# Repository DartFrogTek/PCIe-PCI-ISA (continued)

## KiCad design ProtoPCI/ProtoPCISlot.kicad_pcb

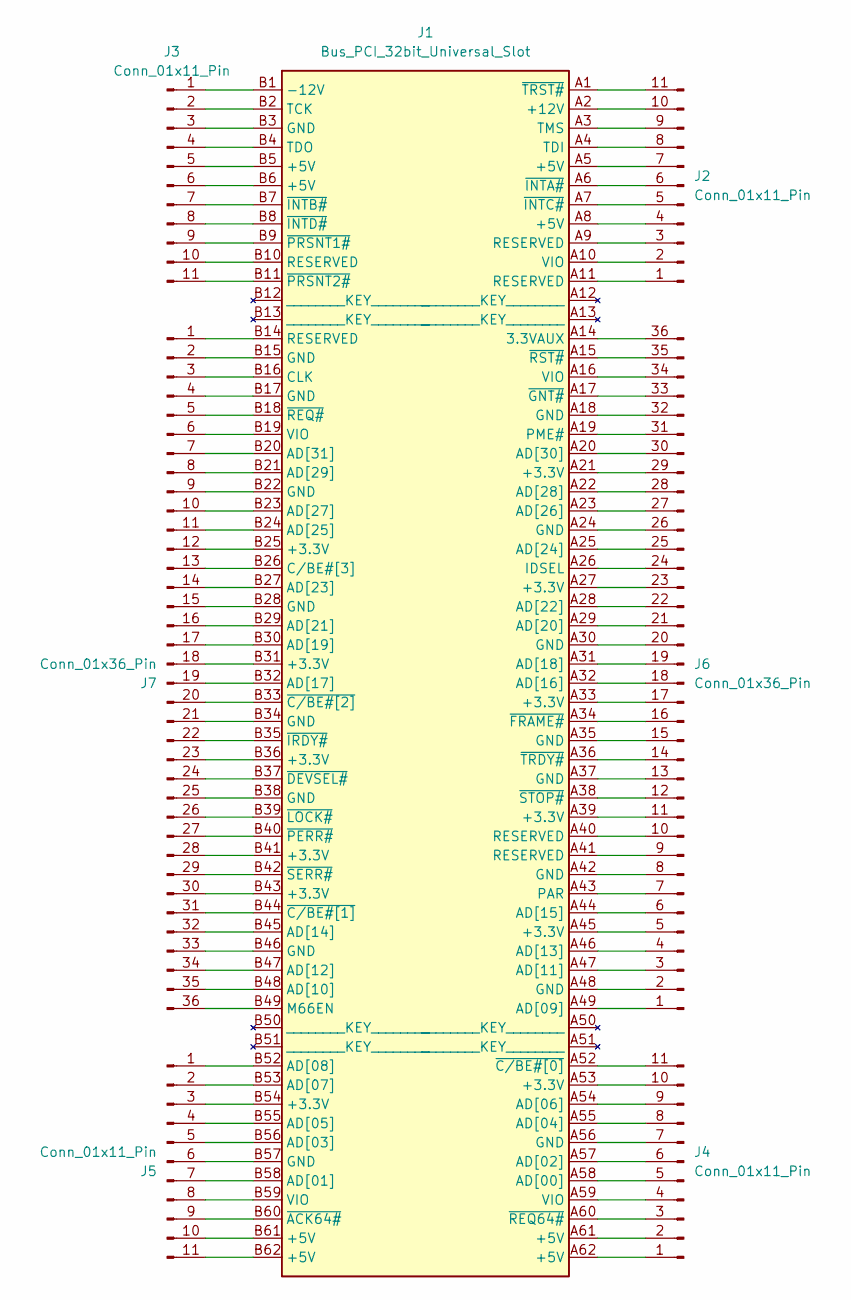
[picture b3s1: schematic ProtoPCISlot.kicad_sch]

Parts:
J1: Bus_PCI_32bit_Universal_Slot; 51451541
J2, J3, J4, J5: Conn_01x11_Pin; PinHeader_1x11_P2.54mm_Vertical
J6, J7: Conn_01x36_Pin; PinHeader_1x36_P2.54mm_Vertical

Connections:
unnamed: J1.A14 (3.3VAUX), J6.36
unnamed: J1.A2 (+12V), J2.10
unnamed: J1.B1 (-12V), J3.1
unnamed: J1.A58 (AD[00]), J4.5
unnamed: J1.B58 (AD[01]), J5.7
unnamed: J1.A57 (AD[02]), J4.6
unnamed: J1.B56 (AD[03]), J5.5
unnamed: J1.A55 (AD[04]), J4.8
unnamed: J1.B55 (AD[05]), J5.4
unnamed: J1.A54 (AD[06]), J4.9
unnamed: J1.B53 (AD[07]), J5.2
unnamed: J1.B52 (AD[08]), J5.1
unnamed: J1.A49 (AD[09]), J6.1
unnamed: J1.B48 (AD[10]), J7.35
unnamed: J1.A47 (AD[11]), J6.3
unnamed: J1.B47 (AD[12]), J7.34
unnamed: J1.A46 (AD[13]), J6.4
unnamed: J1.B45 (AD[14]), J7.32
unnamed: J1.A44 (AD[15]), J6.6
unnamed: J1.A32 (AD[16]), J6.18
unnamed: J1.B32 (AD[17]), J7.19
unnamed: J1.A31 (AD[18]), J6.19
unnamed: J1.B30 (AD[19]), J7.17
unnamed: J1.A29 (AD[20]), J6.21
unnamed: J1.B29 (AD[21]), J7.16
unnamed: J1.A28 (AD[22]), J6.22
unnamed: J1.B27 (AD[23]), J7.14
unnamed: J1.A25 (AD[24]), J6.25
unnamed: J1.B24 (AD[25]), J7.11
unnamed: J1.A23 (AD[26]), J6.27
unnamed: J1.B23 (AD[27]), J7.10
unnamed: J1.A22 (AD[28]), J6.28
unnamed: J1.B21 (AD[29]), J7.8
unnamed: J1.A20 (AD[30]), J6.30
unnamed: J1.B20 (AD[31]), J7.7
unnamed: J1.B16 (CLK), J7.3
unnamed: J1.B26 (C/BE#[3]), J7.13
unnamed: J1.A26 (IDSEL), J6.24
unnamed: J1.B49 (M66EN), J7.36
unnamed: J1.A43 (PAR), J6.7
unnamed: J1.A19 (PME#), J6.31
unnamed: J1.B2 (TCK), J3.2
unnamed: J1.A4 (TDI), J2.8
unnamed: J1.B4 (TDO), J3.4
unnamed: J1.A3 (TMS), J2.9
unnamed: J1.B60 (~ACK64#), J5.9
unnamed: J1.A52 (~C/BE#[0]), J4.11
unnamed: J1.B44 (~C/BE#[1]), J7.31
unnamed: J1.B33 (~C/BE#[2]), J7.20
unnamed: J1.B37 (~DEVSEL#), J7.24
unnamed: J1.A34 (~FRAME#), J6.16
unnamed: J1.A17 (~GNT#), J6.33
unnamed: J1.A6 (~INTA#), J2.6
unnamed: J1.B7 (~INTB#), J3.7
unnamed: J1.A7 (~INTC#), J2.5
unnamed: J1.B8 (~INTD#), J3.8
unnamed: J1.B35 (~IRDY#), J7.22
unnamed: J1.B39 (~LOCK#), J7.26
unnamed: J1.B40 (~PERR#), J7.27
unnamed: J1.B9 (~PRSNT1#), J3.9
unnamed: J1.B11 (~PRSNT2#), J3.11
unnamed: J1.A60 (~REQ64#), J4.3
unnamed: J1.B18 (~REQ#), J7.5
unnamed: J1.A15 (~RST#), J6.35
unnamed: J1.B42 (~SERR#), J7.29
unnamed: J1.A38 (~STOP#), J6.12
unnamed: J1.A36 (~TRDY#), J6.14
unnamed: J1.A1 (~TRST#), J2.11
unnamed: J1.A11 (RESERVED), J2.1
unnamed: J1.A10 (VIO), J2.2
unnamed: J1.A9 (RESERVED), J2.3
unnamed: J1.A8 (+5V), J2.4
unnamed: J1.A5 (+5V), J2.7
unnamed: J1.B3 (GND), J3.3
unnamed: J1.B5 (+5V), J3.5
unnamed: J1.B6 (+5V), J3.6
unnamed: J1.B10 (RESERVED), J3.10
unnamed: J1.A62 (+5V), J4.1
unnamed: J1.A61 (+5V), J4.2
unnamed: J1.A59 (VIO), J4.4
unnamed: J1.A56 (GND), J4.7
unnamed: J1.A53 (+3.3V), J4.10
unnamed: J1.B54 (+3.3V), J5.3
unnamed: J1.B57 (GND), J5.6
unnamed: J1.B59 (VIO), J5.8
unnamed: J1.B61 (+5V), J5.10
unnamed: J1.B62 (+5V), J5.11
unnamed: J1.A48 (GND), J6.2
unnamed: J1.A45 (+3.3V), J6.5
unnamed: J1.A42 (GND), J6.8
unnamed: J1.A41 (RESERVED), J6.9
unnamed: J1.A40 (RESERVED), J6.10
unnamed: J1.A39 (+3.3V), J6.11
unnamed: J1.A37 (GND), J6.13
unnamed: J1.A35 (GND), J6.15
unnamed: J1.A33 (+3.3V), J6.17
unnamed: J1.A30 (GND), J6.20
unnamed: J1.A27 (+3.3V), J6.23
unnamed: J1.A24 (GND), J6.26
unnamed: J1.A21 (+3.3V), J6.29
unnamed: J1.A18 (GND), J6.32
unnamed: J1.A16 (VIO), J6.34
unnamed: J1.B14 (RESERVED), J7.1
unnamed: J1.B15 (GND), J7.2
unnamed: J1.B17 (GND), J7.4
unnamed: J1.B19 (VIO), J7.6
unnamed: J1.B22 (GND), J7.9
unnamed: J1.B25 (+3.3V), J7.12
unnamed: J1.B28 (GND), J7.15
unnamed: J1.B31 (+3.3V), J7.18
unnamed: J1.B34 (GND), J7.21
unnamed: J1.B36 (+3.3V), J7.23
unnamed: J1.B38 (GND), J7.25
unnamed: J1.B41 (+3.3V), J7.28
unnamed: J1.B43 (+3.3V), J7.30
unnamed: J1.B46 (GND), J7.33

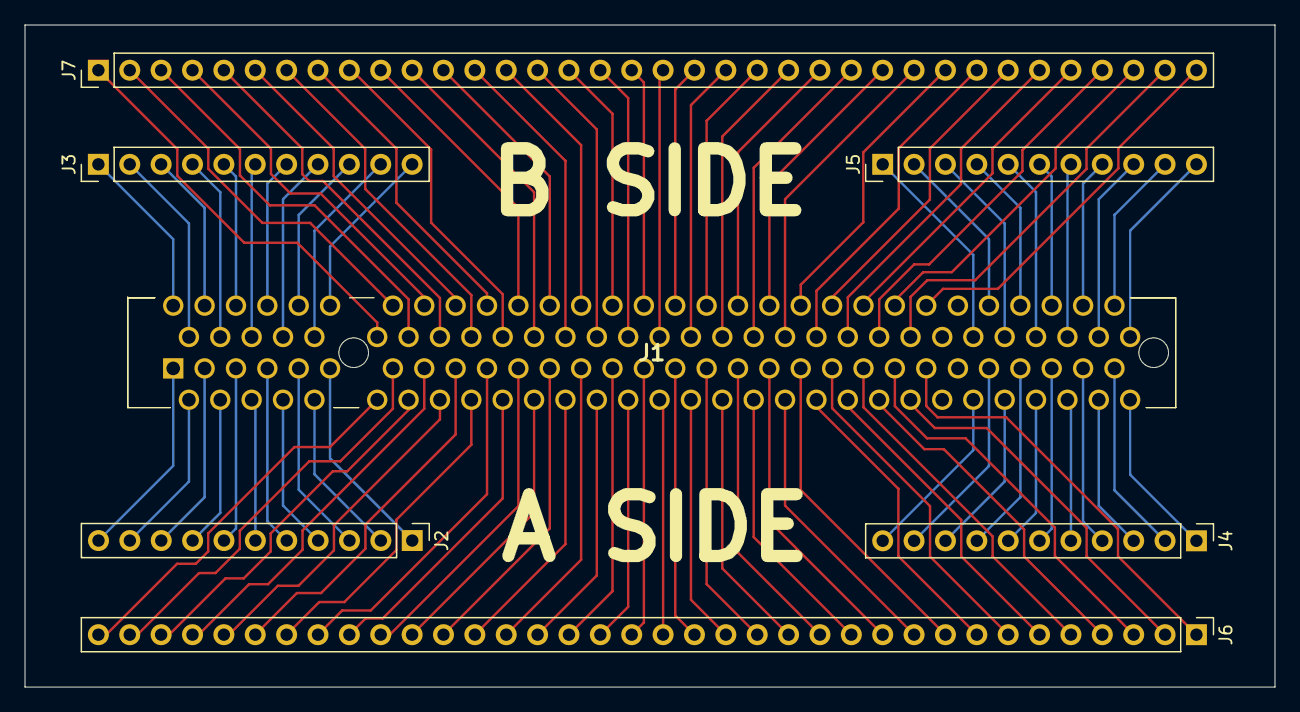
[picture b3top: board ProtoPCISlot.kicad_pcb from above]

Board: 2 copper layers, 101.2 x 53.6 mm, 7 parts (0 on the bottom side), 116 nets.

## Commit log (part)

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2025-04-26 Reorg
2025-04-27 ISA8888 rev00
2025-04-27 Rev 00
2025-04-28 Testing ACPI Compilation
2025-04-29 Temp
2025-04-29 Add MB PPDMA redirect and PPDMA over PCI Configuration
2025-04-30 Routing Test + MAX660
2025-05-02 Boilerplate for AT24C02 ConfigTool and Pico Programmer
2025-05-04 IT8888 Driver / ConfigTool Test
2025-05-19 IRQ9=IRQ2 Errata
2025-05-19 Errata 1 NOWS# and IOCHRDY
2025-05-26 Add LM7905 option for -5v instead of MAX660
2025-05-26 New SCH sheet "Power and Configuration"
2025-05-26 Fixup Power/Config Sheet and update PCB with info from P/C sheet
2025-05-27 Fix negative cap orientations in SCH
2025-05-29 Footprint fix and auto-routed
2025-05-29 PCI Breakout Proto
2025-05-30 Proto PCI Slot/Edge Rev0
2025-06-06 PCI Proto Stuff
2025-06-06 Errata 1 and DRQ Pull Down Fix
2025-06-07 IT8888G Symbol and Footprint
    TODO: Finish Symbol to match [A1-A14, ... P1-P14] pin names instead of [1-160]
2025-06-07 Footprint Updates: ISA TH and Mictor38 Breakout
2025-06-08 ISA8888 PCB update
2025-06-08 BGA-160 to QFP-160 Adapter
    Allows for IT8888G BGA chip to be soldered this adapter. Then the adapter can be soldered to ISA8888 in place of IT8888F.
2025-06-09 Initial BGA to QFP Adapter for QFP replacement via BGA
2025-06-10 BGA/QFP Adapter Setup
2025-06-10 BGA/QFP Adapter Two Layer Setup
2025-06-10 BGA/QFP Adapter Two Layer Baseline
2025-06-10 Finalized BGA/QFP Adapter (TwoLayer File *4LayerActual)
2025-06-13 ISA8888 Prototype Rev 00
2025-06-13 Images
2025-06-13 ImagesHalfSize
2025-06-20 Pico AT24C02 Programmer. "main.c" Uses new pathway via "intel_hex_config.h"
2025-06-22 Windows Driver for PCI Config Cycles
2025-06-22 Windows/Linux Driver for PCI Config Cycles
2025-08-23 GPL WDM Driver
    Gravis UltraSound WDM Driver Project:
    https://popelka.ms.mff.cuni.cz/~stoupa/gus/
2025-08-24 ite8888 configuration driver (not compiled)
2025-08-28 update programmer for gus and reorg
2025-08-29 Comp'd XP WinIO Config Tool + EEPROM Stuff
2025-08-30 Reorg / ISA Detect Tool / ITE8888 Config Tools
2025-08-31 Add configs, update DOS code
    TODO: Finish Windows/DOS SUB/POS decoding in compiled presets.
2025-09-14 82801 and 21152
2025-09-14 21152 dual configs
2025-09-29 cfg+dos16bit
2025-10-20 add pnp isa docs
2026-05-07 Revise PCIe support details in README
    Updated PCIe support section with new information and removed outdated content.
2026-05-11 Ignore this
2026-05-11 ignore this again
2026-05-11 Ignore Thrice
2026-05-11 Ignore Forth
2026-05-11 ignore fifth time
2026-05-12 ignore sixth
2026-05-12 ignore - first crash fx fix
2026-05-13 ignore - install rebuild script
2026-05-13 ignore - fix scripts
2026-05-13 driver works, vdma8 time
2026-05-13 ddma cfg and trace
2026-05-13 ignore -
2026-05-13 ignore - temp
2026-05-13 super ignore - unfortunate
2026-05-17 Update README to remove obsolete PCIe support details
    Removed outdated information regarding PCIe support and reverse engineering efforts.
2026-05-17 ignore - small update
2026-05-19 ignore
2026-05-19 ignore 2
2026-05-19 ignore 3
2026-05-19 :godmode: ignore - high dram working - doom music plays
2026-05-19 :godmode: gus-play-safe 0x8240 .\test.wav
    gus-play-safe 0x8240 .\test.wav
    gus-play-safe 0x8240 .\test.wav --verify
    gus-play-safe 0x8240 .\test.wav --freq 0x03c0
    gus-play-safe 0x8240 .\test.wav --verify --no-play
2026-05-19 :godmode: freeze known good cpu port dram
    .\dist\Debug_x64\it8888ctl.exe gus-known-good-selftest-safe 0x8240
    .\dist\Debug_x64\it8888ctl.exe gus-known-good-selftest-safe 0x8240 .\test.wav
2026-05-19 :feelsgood: dma/ddma is a cyberdemon
2026-05-22 :godmode: ignore - DDMA :godmode:
    .\install_rebuild_it8888vdma_signed.ps1 Debug x64
    .\dist\Debug_x64\it8888ctl.exe init
    .\dist\Debug_x64\it8888ctl.exe bridge-iowin 0 28 3 0x8000 0x8fff
    .\dist\Debug_x64\it8888ctl.exe bridge-iowin 3 0 0 0x8000 0x8fff
    .\dist\Debug_x64\it8888ctl.exe cfgwrite 0x5C 4 0xe3008340
    .\dist\Debug_x64\it8888ctl.exe cfgwrite 0x60 4 0xe2008240
2026-06-05 FPGA not compiled - historical
2026-06-05 ignore this temp
2026-06-06 initial dos application started
2026-06-19 Add DFT_FDC_WIN10 KMDF floppy driver pass-1
    Introduce a new DFT_FDC_WIN10 pass‑1 KMDF project: adds a Visual Studio solution and project files, kernel driver sources/headers (dftfdc), a user‑mode control tool (dftfdcctl), INF and distribution 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
2026-06-19 Add build/sign scripts and KMDF 1.9
    Add build_sign_deploy.bat and a comprehensive PowerShell build_sign_deploy.ps1 to automate KMDF detection, patch the INF, run build, create catalog, sign with a local test certificate, and install th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
